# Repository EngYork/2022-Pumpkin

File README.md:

A Pumpkin-shaped lamp using WS2812b LED modules and the cheapest STM32 I could find on Digikey.

The timings are generated - and data fed fast enough - by using the DMA and abusing the SPI (See 2022 Pumpkin Code for details).

Due to component shortages the FTDI USB chip was never fitted or tested by me, although someone told me they tried it and it didn't work - so beware of that.

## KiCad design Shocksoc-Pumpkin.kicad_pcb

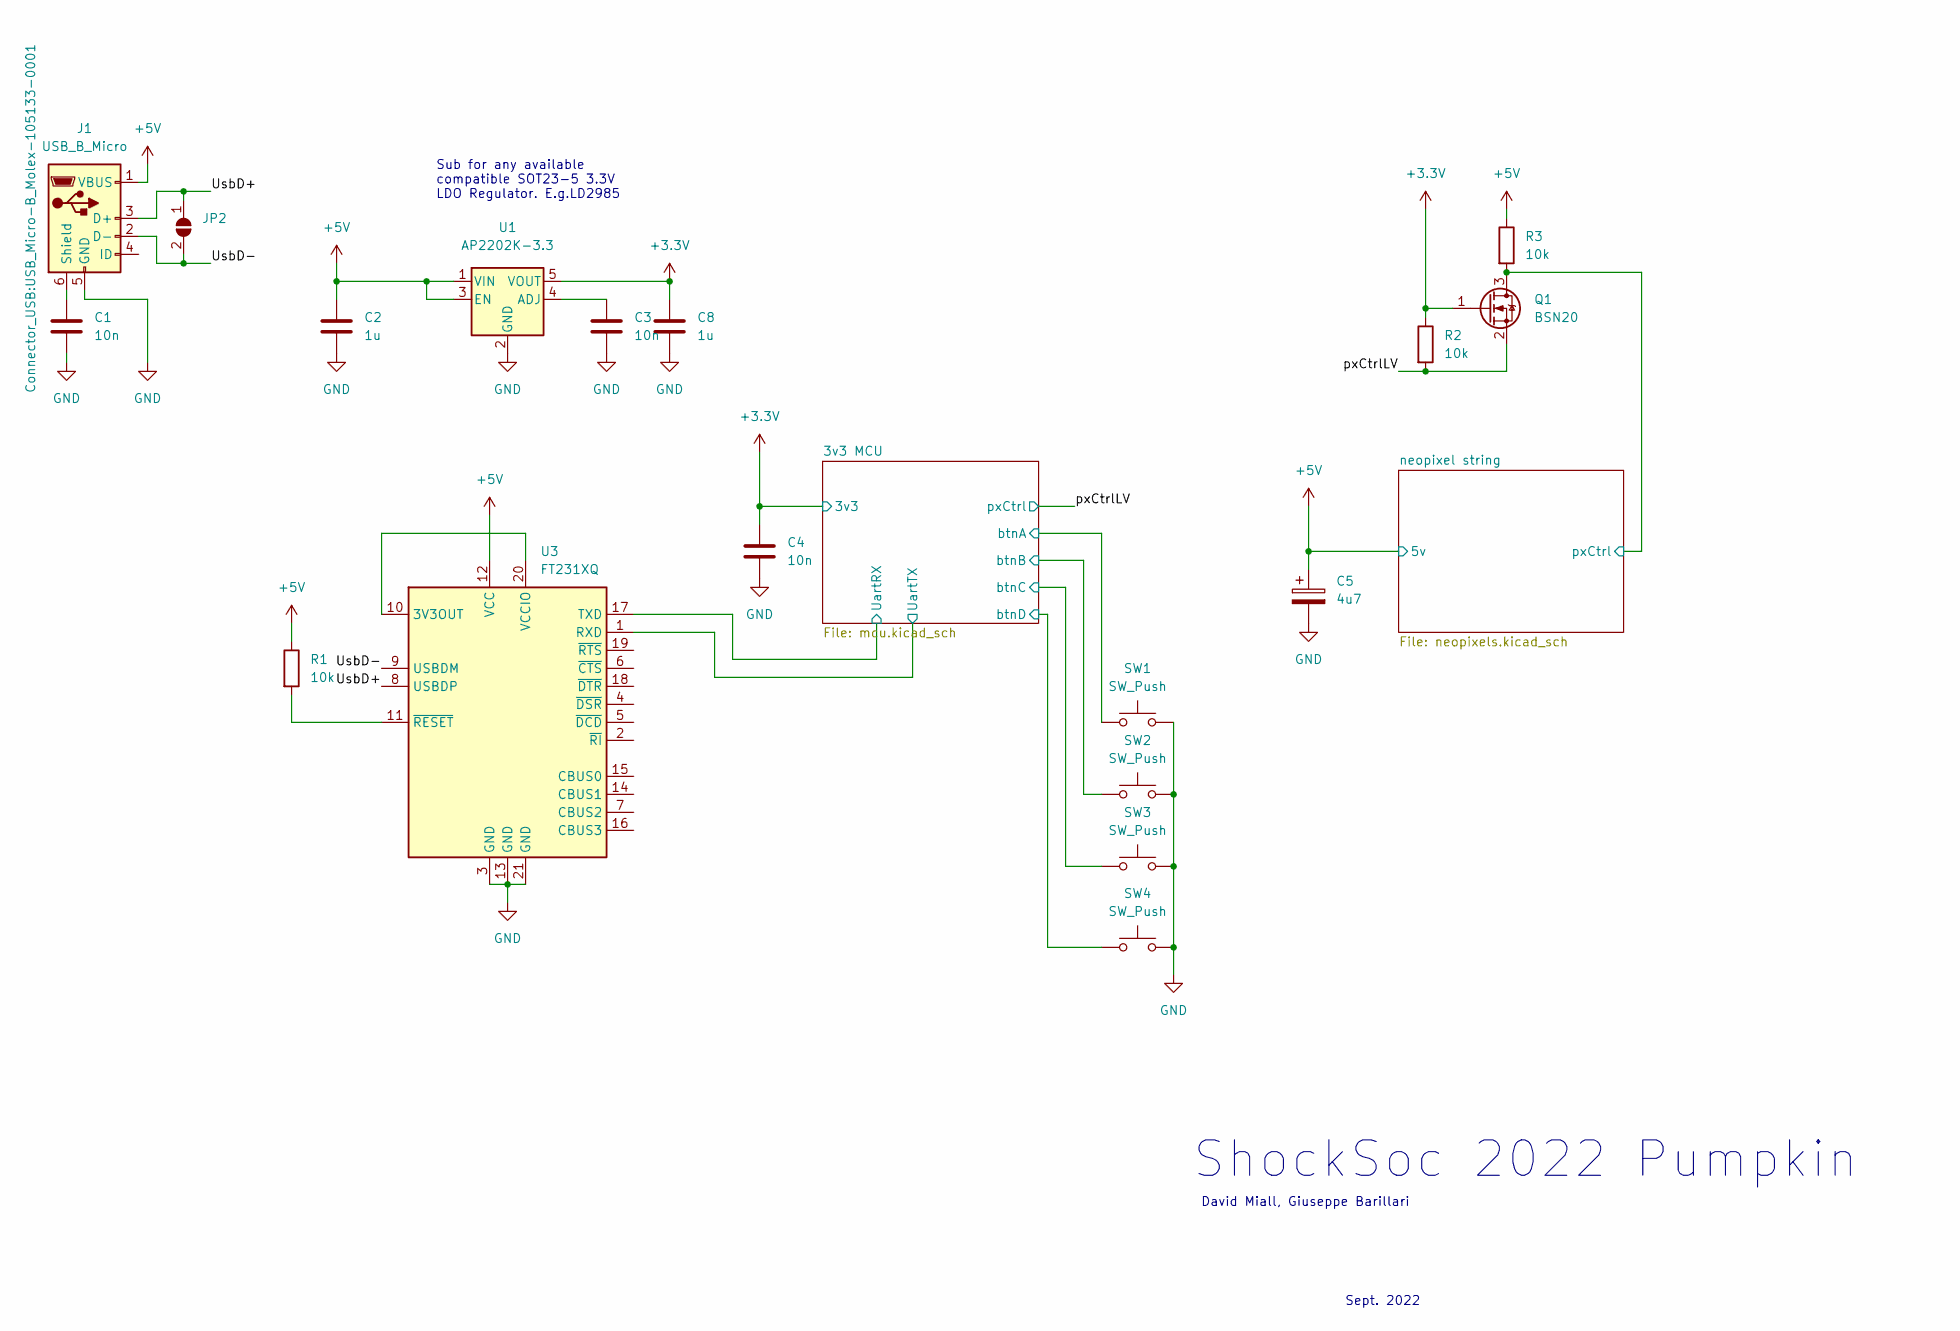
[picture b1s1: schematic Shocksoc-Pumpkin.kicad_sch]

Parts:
C1, C3, C4: 10n; C_0805_2012Metric_Pad1.18x1.45mm_HandSolder
C2, C8: 1u; C_0805_2012Metric_Pad1.18x1.45mm_HandSolder
C5: 4u7; C_0805_2012Metric_Pad1.18x1.45mm_HandSolder
J1: USB_B_Micro; USB_Micro-B_Molex-105133-0001
JP2: SolderJumper_2_Open; SolderJumper-2_P1.3mm_Open_RoundedPad1.0x1.5mm
Q1: BSN20; SOT-23
R1, R2, R3: 10k; R_0805_2012Metric_Pad1.20x1.40mm_HandSolder
SW1, SW2, SW3, SW4: SW_Push; SW_Push_1P1T_NO_6x6mm_H9.5mm
U1: AP2202K-3.3; SOT-23-5
U3: FT231XQ; QFN-20-1EP_4x4mm_P0.5mm_EP2.5x2.5mm

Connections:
+3.3V: C4.1, C8.1, Q1.1 (G), R2.1, U1.5 (VOUT); also elsewhere on the board
+5V: C2.1, C5.1, J1.1 (VBUS), R1.1, R3.1, U1.1 (VIN), U1.3 (EN), U3.12 (VCC); also elsewhere on the board
/3v3 MCU/UartRX: U3.17 (TXD); also elsewhere on the board
/3v3 MCU/UartTX: U3.1 (RXD); also elsewhere on the board
/3v3 MCU/btnA: SW1.1; also elsewhere on the board
/3v3 MCU/btnB: SW2.1; also elsewhere on the board
/3v3 MCU/btnC: SW3.1; also elsewhere on the board
/3v3 MCU/btnD: SW4.1; also elsewhere on the board
/UsbD+: J1.3 (D+), JP2.1 (A), U3.8 (USBDP)
/UsbD-: J1.2 (D-), JP2.2 (B), U3.9 (USBDM)
/neopixel string/pxCtrl: Q1.3 (D), R3.2; also elsewhere on the board
/pxCtrlLV: Q1.2 (S), R2.2; also elsewhere on the board
GND: C1.2, C2.2, C3.2, C4.2, C5.2, C8.2, J1.5 (GND), SW1.2, SW2.2, SW3.2, SW4.2, U1.2 (GND), U3.3 (GND), U3.13 (GND), U3.21 (GND); also elsewhere on the board
unnamed: C1.1, J1.6 (Shield)
unnamed: C3.1, U1.4 (ADJ)
unnamed: R1.2, U3.11 (~RESET)
unnamed: U3.10 (3V3OUT), U3.20 (VCCIO)

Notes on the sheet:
David Miall, Giuseppe Barillari
Sub for any available compatible SOT23-5 3.3V LDO Regulator. E.g.LD2985
ShockSoc 2022 Pumpkin
Sept. 2022

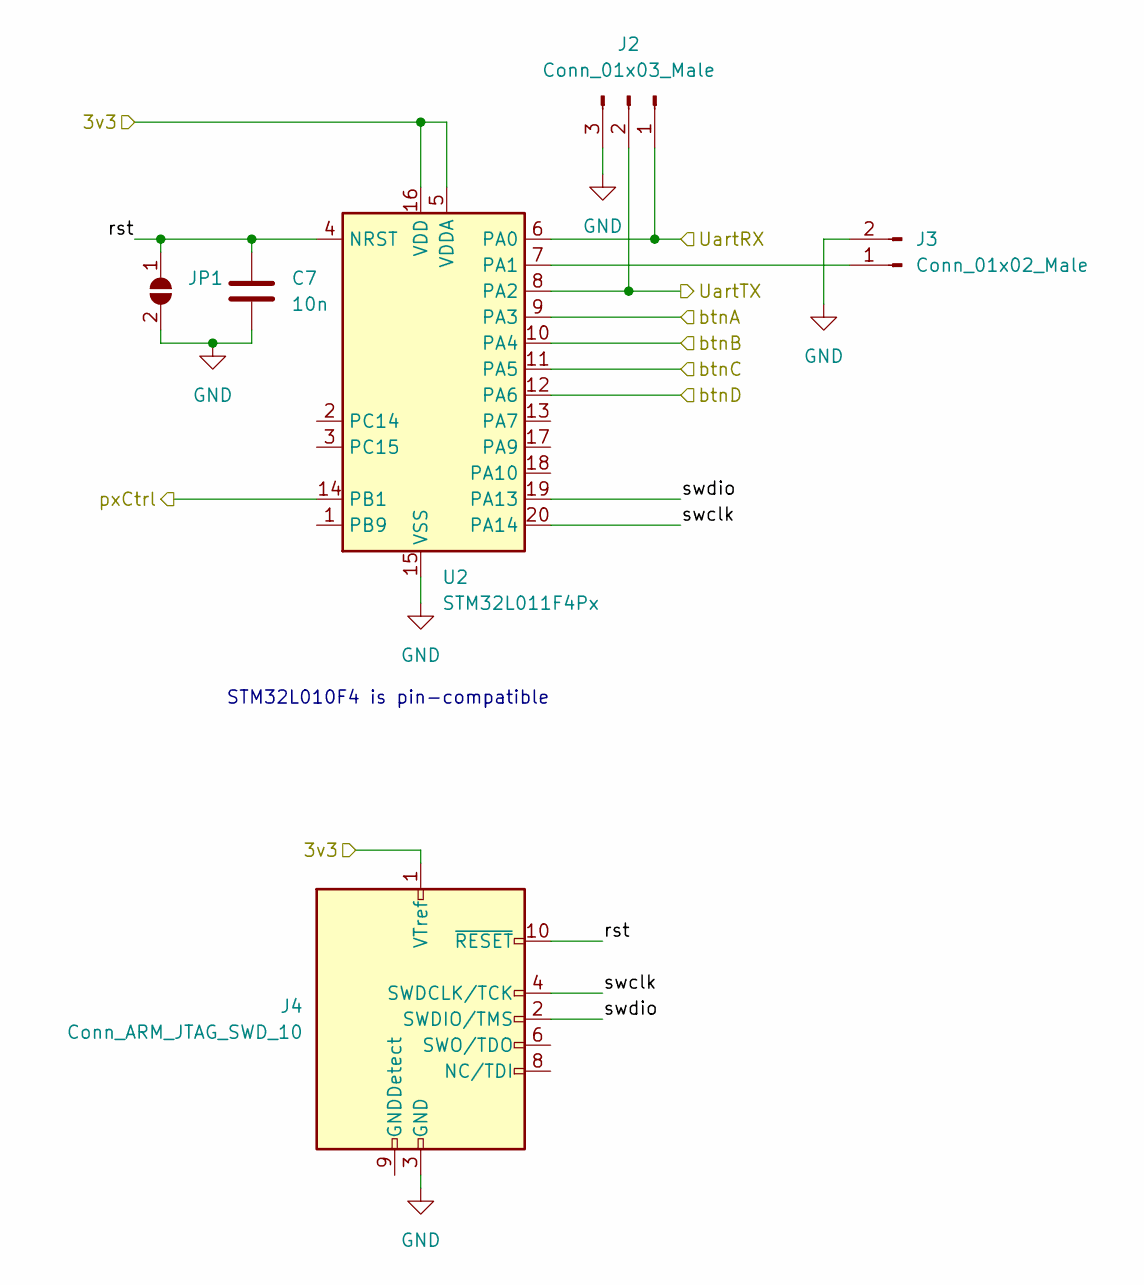
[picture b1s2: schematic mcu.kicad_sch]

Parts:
C7: 10n; C_0805_2012Metric_Pad1.18x1.45mm_HandSolder
J2: Conn_01x03_Male; PinHeader_1x03_P2.54mm_Vertical
J3: Conn_01x02_Male; PinHeader_1x02_P2.54mm_Vertical
J4: Conn_ARM_JTAG_SWD_10; PinHeader_2x05_P1.27mm_Vertical
JP1: SolderJumper_2_Open; SolderJumper-2_P1.3mm_Open_RoundedPad1.0x1.5mm
U2: STM32L011F4Px; TSSOP-20_4.4x6.5mm_P0.65mm

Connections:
+3.3V: J4.1 (VTref), U2.5 (VDDA), U2.16 (VDD); also elsewhere on the board
/3v3 MCU/UartRX: J2.1, U2.6 (PA0); also elsewhere on the board
/3v3 MCU/UartTX: J2.2, U2.8 (PA2); also elsewhere on the board
/3v3 MCU/btnA: U2.9 (PA3); also elsewhere on the board
/3v3 MCU/btnB: U2.10 (PA4); also elsewhere on the board
/3v3 MCU/btnC: U2.11 (PA5); also elsewhere on the board
/3v3 MCU/btnD: U2.12 (PA6); also elsewhere on the board
/3v3 MCU/rst: C7.1, J4.10 (~RESET), JP1.1 (A), U2.4 (NRST)
/3v3 MCU/swclk: J4.4 (SWDCLK/TCK), U2.20 (PA14)
/3v3 MCU/swdio: J4.2 (SWDIO/TMS), U2.19 (PA13)
/pxCtrlLV: U2.14 (PB1); also elsewhere on the board
GND: C7.2, J2.3, J3.2, J4.3 (GND), J4.5 (GND), JP1.2 (B), U2.15 (VSS); also elsewhere on the board
unnamed: J3.1, U2.7 (PA1)

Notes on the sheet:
STM32L010F4 is pin-compatible

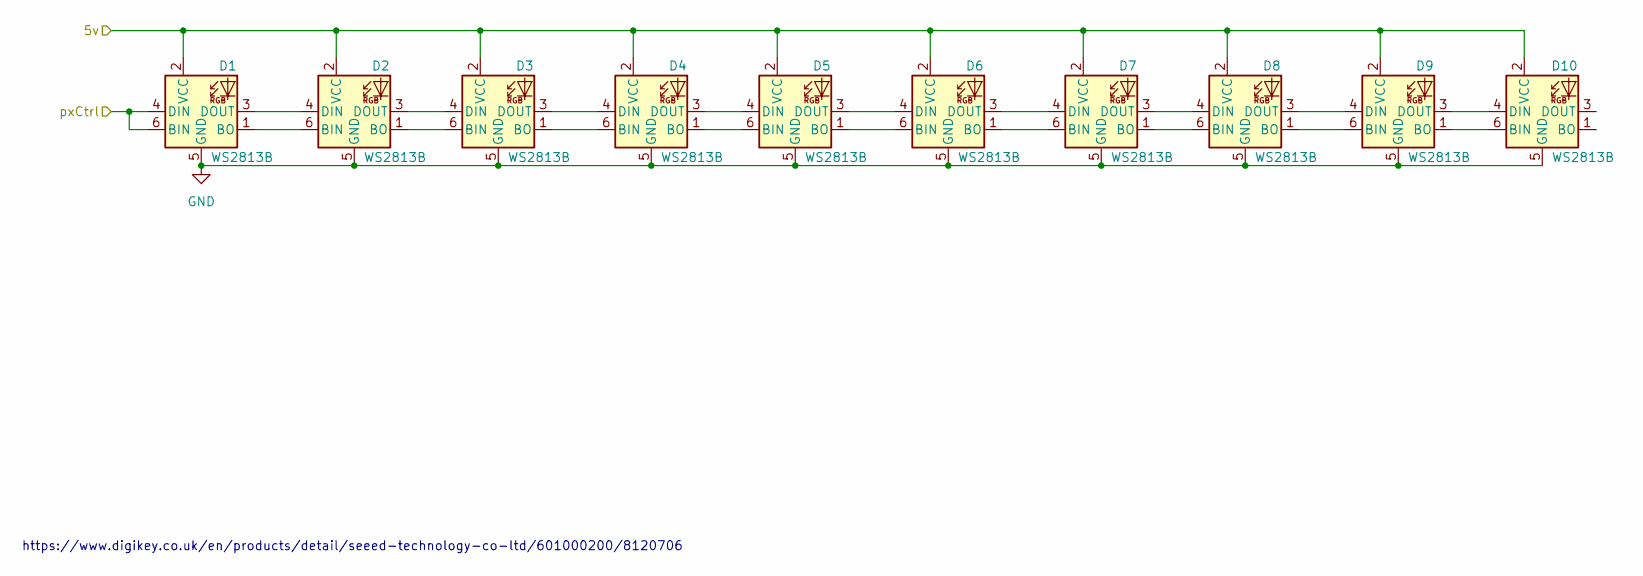
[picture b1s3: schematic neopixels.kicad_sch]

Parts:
D1, D2, D3, D4, D5, D6, D7, D8, D9, D10: WS2813B; LED_WS2813_hand

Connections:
+5V: D1.2 (VCC), D2.2 (VCC), D3.2 (VCC), D4.2 (VCC), D5.2 (VCC), D6.2 (VCC), D7.2 (VCC), D8.2 (VCC), D9.2 (VCC), D10.2 (VCC); also elsewhere on the board
/neopixel string/pxCtrl: D1.4 (DIN), D1.6 (BIN); also elsewhere on the board
GND: D1.5 (GND), D2.5 (GND), D3.5 (GND), D4.5 (GND), D5.5 (GND), D6.5 (GND), D7.5 (GND), D8.5 (GND), D9.5 (GND), D10.5 (GND); also elsewhere on the board
unnamed: D1.1 (BO), D2.6 (BIN)
unnamed: D1.3 (DOUT), D2.4 (DIN)
unnamed: D2.1 (BO), D3.6 (BIN)
unnamed: D2.3 (DOUT), D3.4 (DIN)
unnamed: D3.1 (BO), D4.6 (BIN)
unnamed: D3.3 (DOUT), D4.4 (DIN)
unnamed: D4.1 (BO), D5.6 (BIN)
unnamed: D4.3 (DOUT), D5.4 (DIN)
unnamed: D5.1 (BO), D6.6 (BIN)
unnamed: D5.3 (DOUT), D6.4 (DIN)
unnamed: D6.1 (BO), D7.6 (BIN)
unnamed: D6.3 (DOUT), D7.4 (DIN)
unnamed: D8.1 (BO), D9.6 (BIN)
unnamed: D8.3 (DOUT), D9.4 (DIN)
unnamed: D7.3 (DOUT), D8.4 (DIN)
unnamed: D7.1 (BO), D8.6 (BIN)
unnamed: D9.3 (DOUT), D10.4 (DIN)
unnamed: D9.1 (BO), D10.6 (BIN)

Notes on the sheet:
https://www.digikey.co.uk/en/products/detail/seeed-technology-co-ltd/601000200/8120706

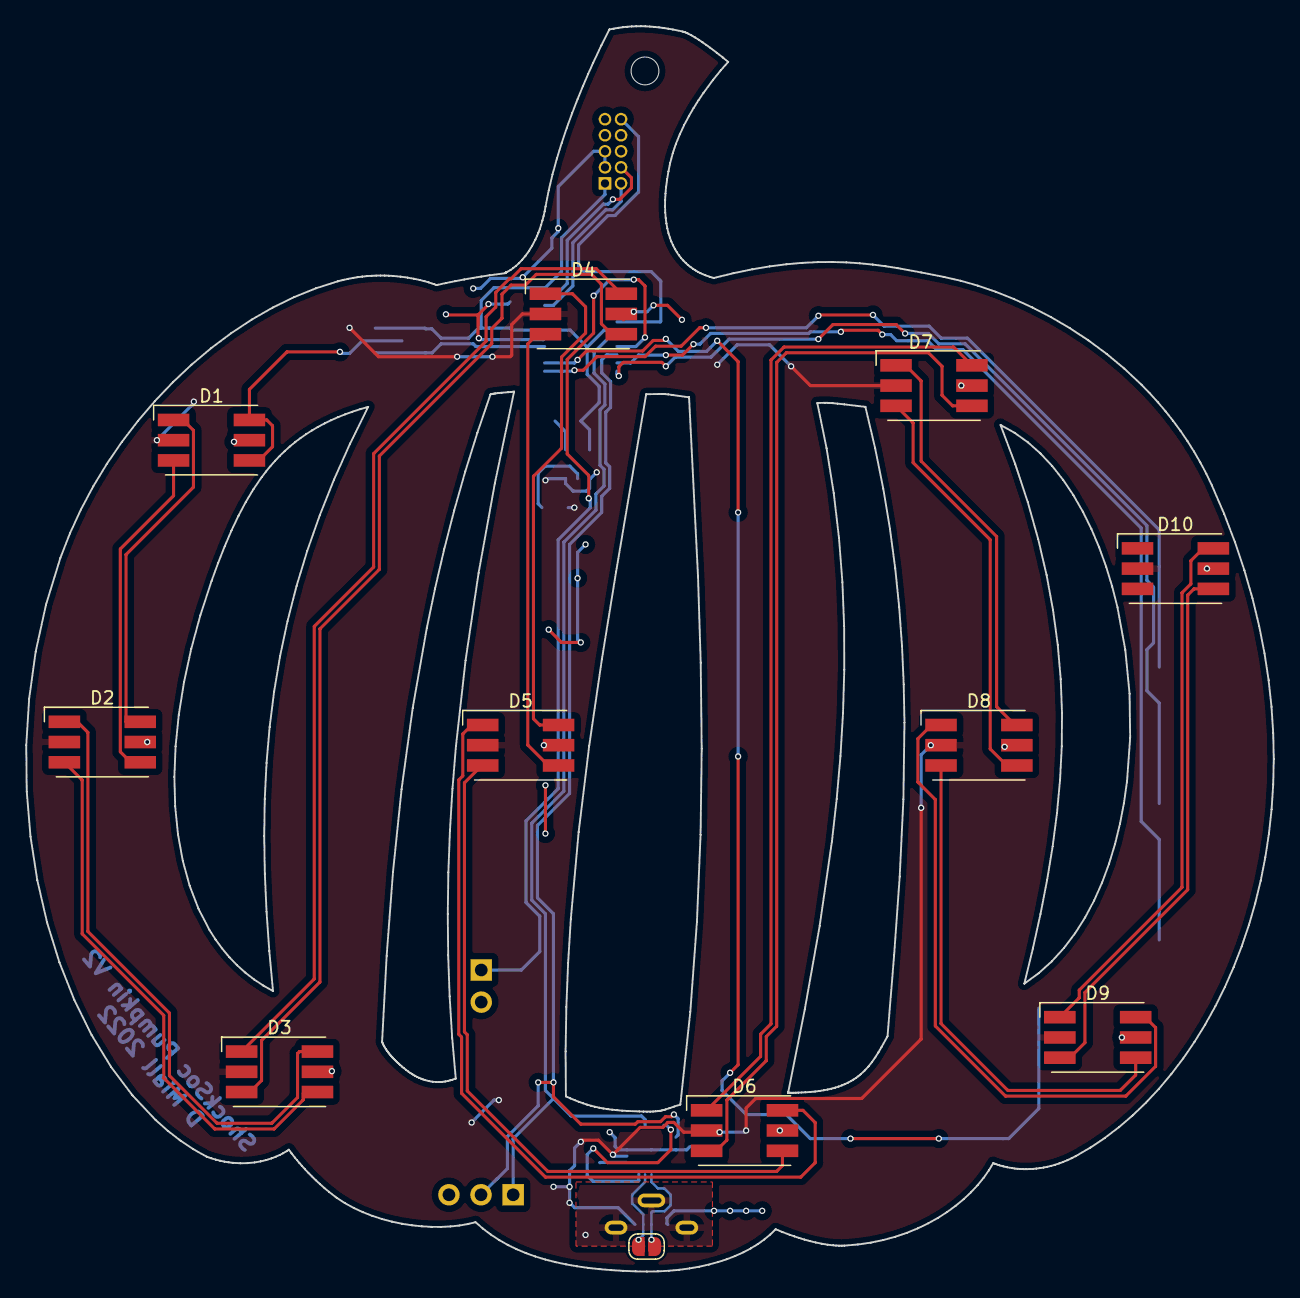
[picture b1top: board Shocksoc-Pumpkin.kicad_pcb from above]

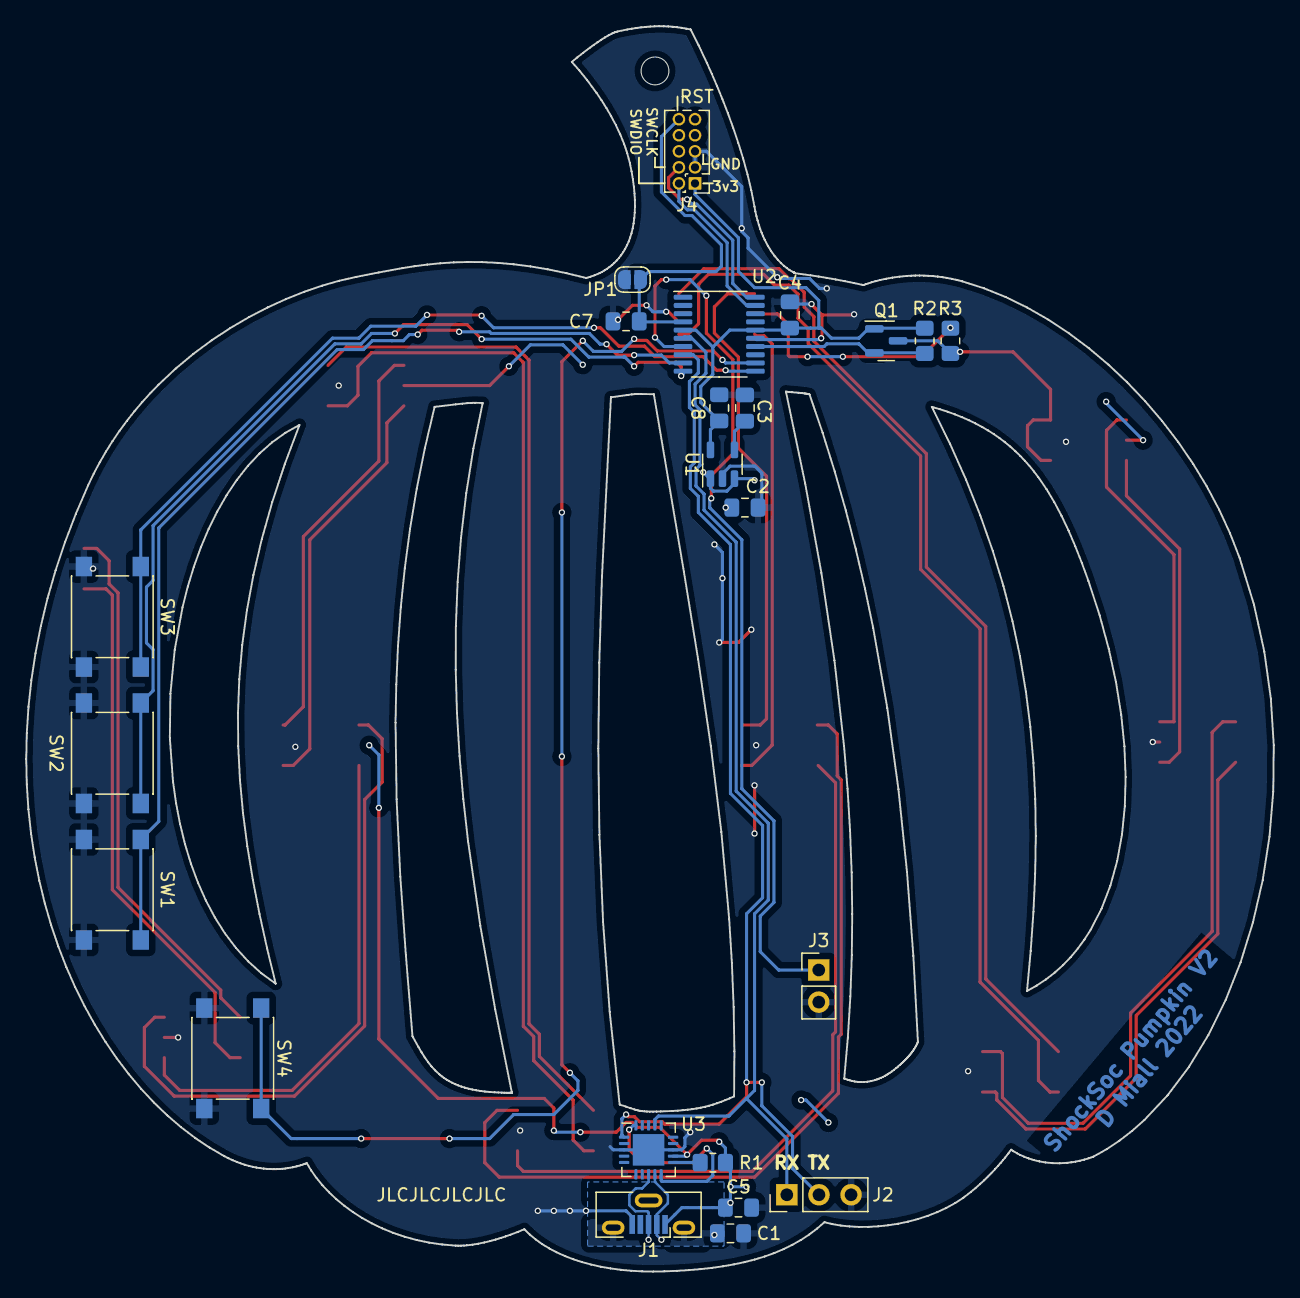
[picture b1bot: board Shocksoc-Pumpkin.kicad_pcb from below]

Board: 2 copper layers, 98.7 x 98.5 mm, 34 parts (23 on the bottom side), 39 nets.

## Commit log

2022-07-31 Initial charging sketch
2022-10-09 Add current files
2022-10-09 Resized pads
2022-10-09 Gerbers
2022-10-09 Add THT debug
2022-11-05 Prod
